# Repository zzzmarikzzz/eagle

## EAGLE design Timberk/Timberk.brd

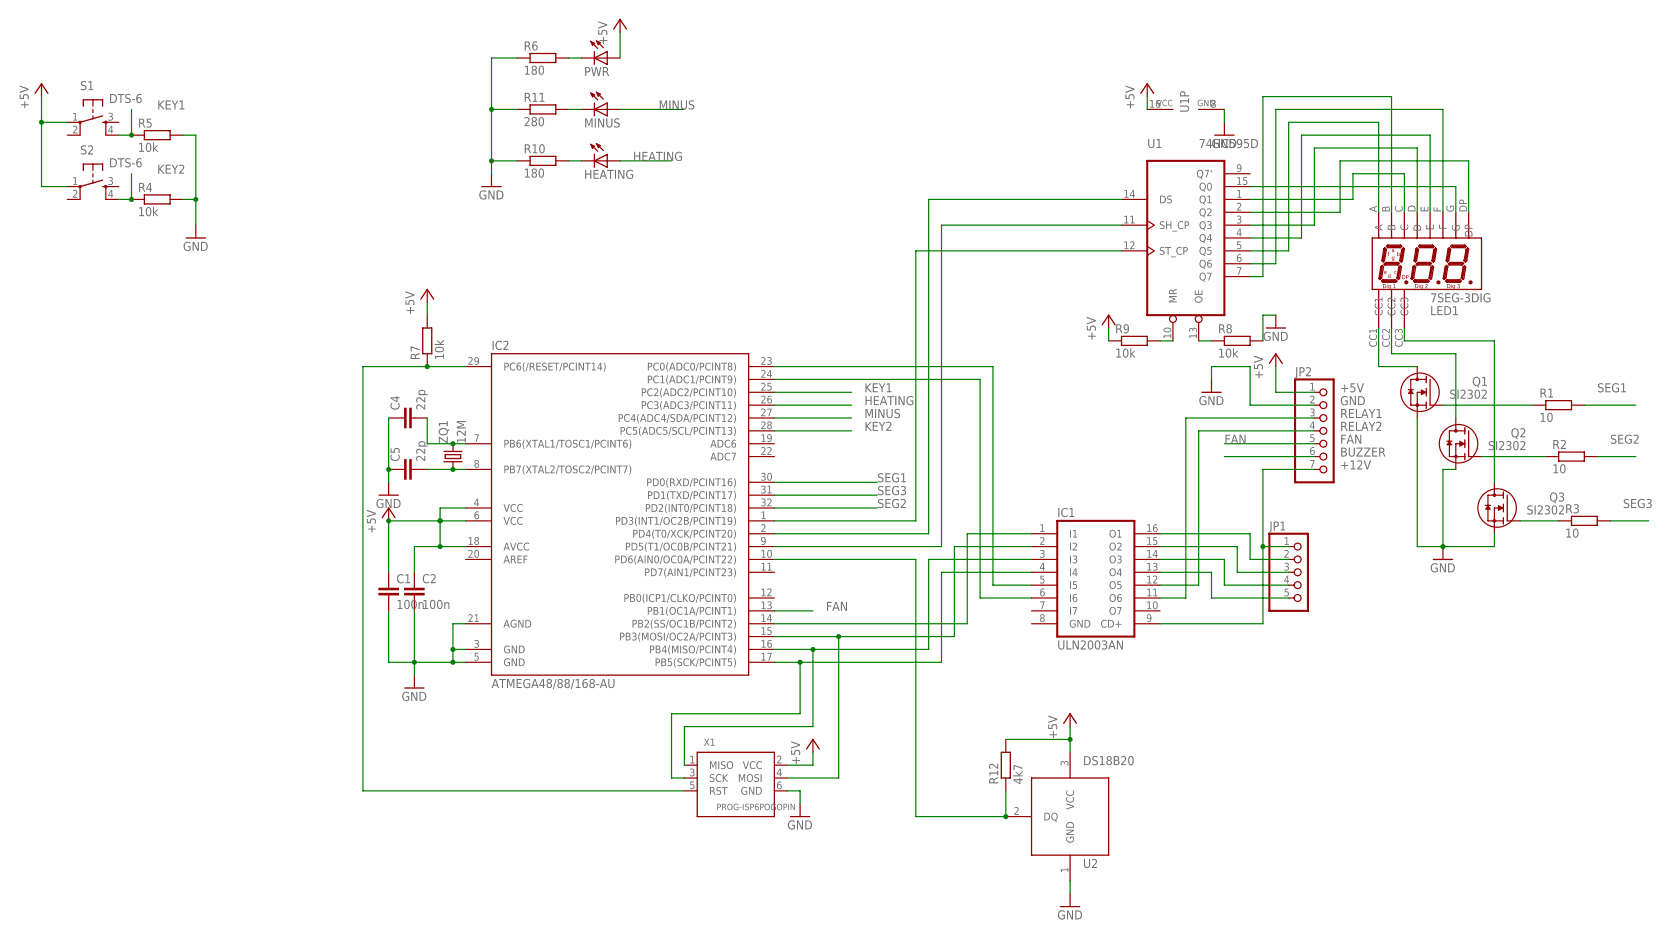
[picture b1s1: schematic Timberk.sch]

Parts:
C1, C2: 100n; C0603
C4, C5: 22p; C0603
HEATING: LED5MM
IC1: ULN2003AN; DIL16
IC2: ATMEGA48/88/168-AU; TQFP32-08
JP1: PINHD-1X5/90; 1X05/90
JP2: PINHD-1X7/90; 1X07/90
LED1: 7SEG-3DIG; 7SEG_3DIG_0.56
MINUS: LED5MM
PWR: LED5MM
Q1, Q2, Q3: SI2302; SOT-23-GSD
R1, R2, R3: 10; R0603
R4, R5, R7, R8, R9: 10k; R0603
R6, R10: 180; R0603
R11: 280; R0603
R12: 4k7; R0603
S1, S2: DTS-6
U1: 74HC595D; SO16
U2: DS18B20; TO92
X1: PROG-ISP6POGOPIN; PROG_POGOPIN
ZQ1: 12M; HC49/S

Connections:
+5V: C1.1, C2.1, IC2.4 (VCC), IC2.6 (VCC), IC2.18 (AVCC), JP2.1, PWR.A, R7.2, R9.1, R12.2, S1.1, S2.1, U1.16 (VCC), U2.3 (VCC), X1.2 (VCC)
+12V: IC1.9 (CD+), JP1.1, JP2.7
BUZZER: JP2.6
FAN: IC2.13 (PB1(OC1A/PCINT1)), JP2.5
GND: C1.2, C2.2, C4.1, C5.1, IC1.8 (GND), IC2.3 (GND), IC2.5 (GND), IC2.21 (AGND), JP2.2, Q1.S, Q2.S, Q3.S, R4.2, R5.2, R6.1, R8.2, R10.1, R11.1, U1.8 (GND), U2.1 (GND), X1.6 (GND)
HEATING: HEATING.A, IC2.26 (PC3(ADC3/PCINT11))
KEY1: IC2.25 (PC2(ADC2/PCINT10)), R5.1, S1.4
KEY2: IC2.28 (PC5(ADC5/SCL/PCINT13)), R4.1, S2.4
MINUS: IC2.27 (PC4(ADC4/SDA/PCINT12)), MINUS.A
unnamed: IC1.13 (O4), JP1.5
unnamed: IC1.14 (O3), JP1.4
unnamed: IC1.15 (O2), JP1.3
unnamed: IC1.16 (O1), JP1.2
unnamed: LED1.C, U1.1 (Q1)
unnamed: LED1.DP, U1.2 (Q2)
unnamed: LED1.G, U1.15 (Q0)
unnamed: LED1.D, U1.3 (Q3)
unnamed: LED1.E, U1.4 (Q4)
unnamed: LED1.A, U1.5 (Q5)
unnamed: LED1.F, U1.6 (Q6)
unnamed: LED1.B, U1.7 (Q7)
unnamed: Q1.G, R1.1
unnamed: Q2.G, R2.1
unnamed: Q3.G, R3.1
unnamed: LED1.CC1, Q1.D
unnamed: LED1.CC2, Q2.D
unnamed: LED1.CC3, Q3.D
unnamed: PWR.K (C), R6.2
unnamed: IC1.1 (I1), IC2.14 (PB2(SS/OC1B/PCINT2))
unnamed: IC1.2 (I2), IC2.15 (PB3(MOSI/OC2A/PCINT3)), X1.4 (MOSI)
unnamed: IC1.6 (I6), IC2.24 (PC1(ADC1/PCINT9))
unnamed: IC1.3 (I3), IC2.16 (PB4(MISO/PCINT4)), X1.1 (MISO)
unnamed: IC1.4 (I4), IC2.17 (PB5(SCK/PCINT5)), X1.3 (SCK)
unnamed: IC2.29 (PC6(/RESET/PCINT14)), R7.1, X1.5 (RST)
unnamed: R9.2, U1.10 (MR)
unnamed: IC2.1 (PD3(INT1/OC2B/PCINT19)), U1.12 (ST_CP)
unnamed: C5.2, IC2.8 (PB7(XTAL2/TOSC2/PCINT7)), ZQ1.1
unnamed: C4.2, IC2.7 (PB6(XTAL1/TOSC1/PCINT6)), ZQ1.2
unnamed: R8.1, U1.13 (OE)
unnamed: IC2.2 (PD4(T0/XCK/PCINT20)), U1.14 (DS)
unnamed: IC2.9 (PD5(T1/OC0B/PCINT21)), U1.11 (SH_CP)
unnamed: IC1.5 (I5), IC2.23 (PC0(ADC0/PCINT8))
unnamed: HEATING.K (C), R10.2
unnamed: MINUS.K (C), R11.2
unnamed: IC2.10 (PD6(AIN0/OC0A/PCINT22)), R12.1, U2.2 (DQ)
RELAY1: IC1.11 (O6), JP2.3
RELAY2: IC1.12 (O5), JP2.4
SEG1: IC2.30 (PD0(RXD/PCINT16)), R1.2
SEG2: IC2.32 (PD2(INT0/PCINT18)), R2.2
SEG3: IC2.31 (PD1(TXD/PCINT17)), R3.2

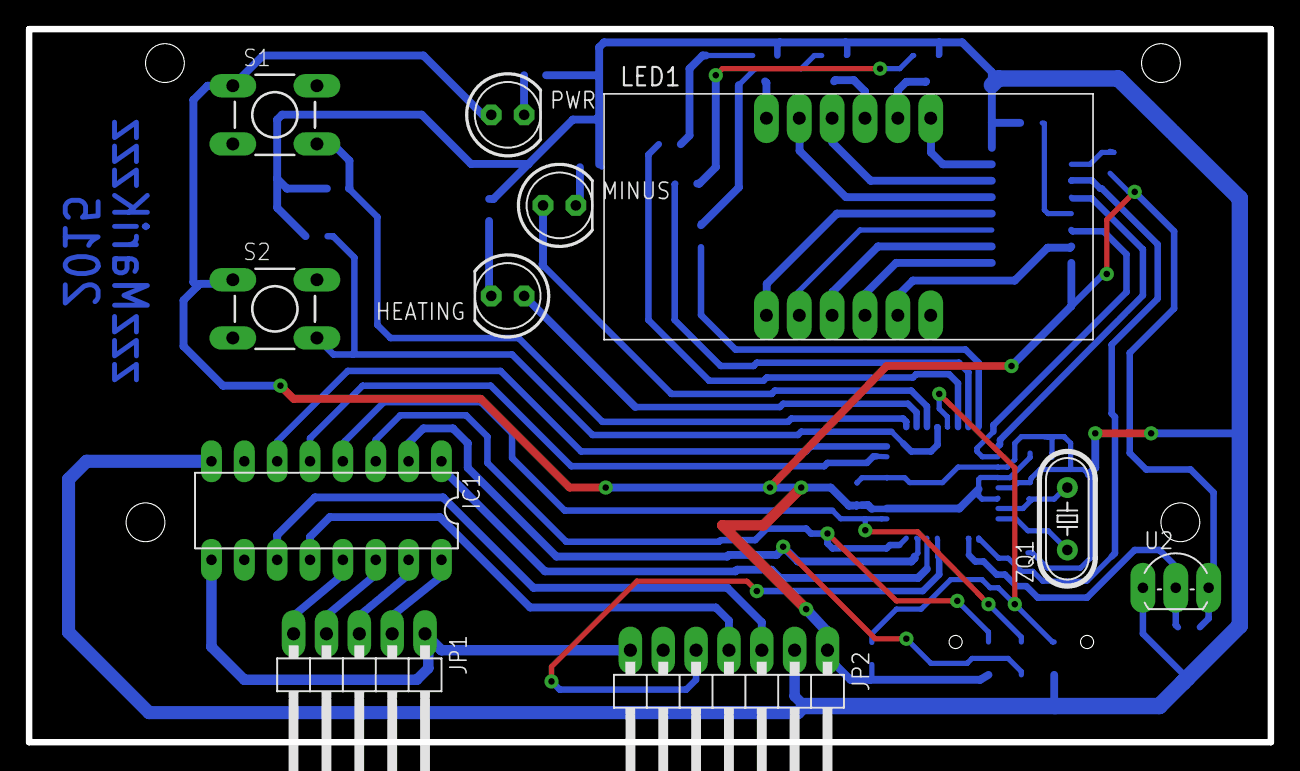
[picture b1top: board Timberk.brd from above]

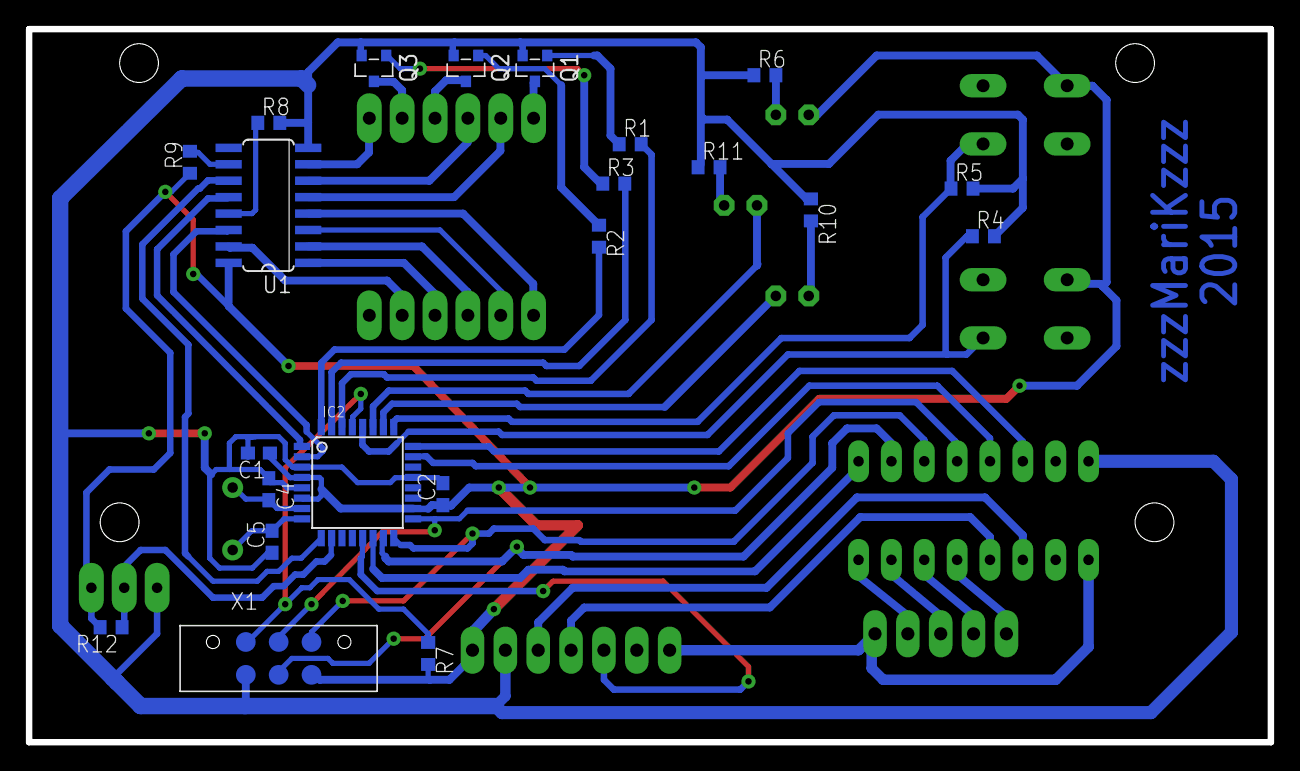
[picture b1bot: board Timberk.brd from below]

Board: 2 copper layers, 96.0 x 55.1 mm, 33 parts (22 on the bottom side), 49 nets.

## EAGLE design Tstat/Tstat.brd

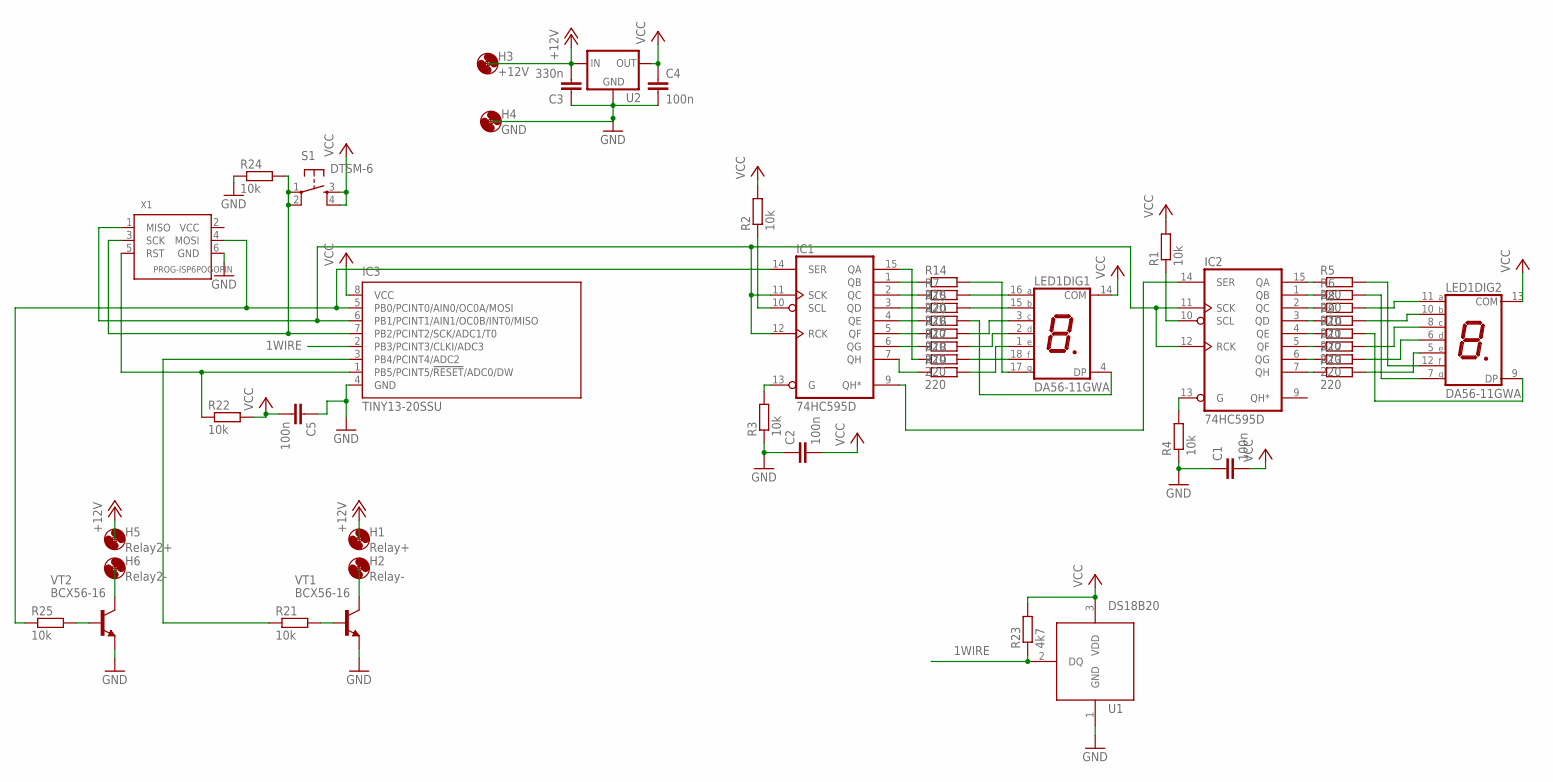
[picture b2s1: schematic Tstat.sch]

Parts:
C1, C2, C4, C5: 100n; C0805
C3: 330n; C0805
H1: Relay+; 3,0
H2: Relay-; 3,0
H3: +12V; 3,0
H4: GND; 3,0
H5: Relay2+; 3,0
H6: Relay2-; 3,0
IC1, IC2: 74HC595D; SO16
IC3: TINY13-20SSU; 8S1
LED1: DA56-11GWA; DA56
R1, R2, R3, R4, R21, R22, R24, R25: 10k; R0603
R5, R6, R7, R8, R9, R10, R11, R12, R13, R14, R15, R16, R17, R18, R19, R20: 220; R0603
R23: 4k7; R0603
S1: DTSM-6
U1: DS18B20; TO92
U2: L78XX/TO263; TO263
VT1, VT2: BCX56-16; SOT89-BCE
X1: PROG-ISP6POGOPIN; PROG_POGOPIN

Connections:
1WIRE: IC3.2 (PB3/PCINT3/CLKI/ADC3), R23.1, U1.2 (DQ)
+12V: C3.2, H1.P$1, H3.P$1, H5.P$1, U2.1 (IN)
GND: C1.1, C2.1, C3.1, C4.2, C5.1, H4.P$1, IC1.8 (GND), IC2.8 (GND), IC3.4 (GND), R3.1, R4.1, R24.1, U1.1 (GND), U2.3 (GND), VT1.E, VT2.E, X1.6 (GND)
unnamed: IC1.15 (QA), R18.1
unnamed: LED1.17 (G), R14.2
unnamed: LED1.16 (A), R7.2
unnamed: LED1.15 (B), R15.2
unnamed: LED1.4 (DP), R20.2
unnamed: LED1.3 (C), R16.2
unnamed: LED1.2 (D), R17.2
unnamed: LED1.1 (E), R19.2
unnamed: LED1.12 (F), R5.2
unnamed: LED1.7 (G), R6.2
unnamed: LED1.11 (A), R8.2
unnamed: LED1.10 (B), R9.2
unnamed: LED1.9 (DP), R10.2
unnamed: LED1.8 (C), R11.2
unnamed: LED1.6 (D), R12.2
unnamed: LED1.5 (E), R13.2
unnamed: IC1.9 (QH*), IC2.14 (SER)
unnamed: IC2.10 (SCL), R1.1
unnamed: IC2.13 (G), R4.2
unnamed: IC1.13 (G), R3.2
unnamed: IC1.10 (SCL), R2.1
unnamed: IC2.15 (QA), R5.1
unnamed: IC1.11 (SCK), IC1.12 (RCK), IC2.11 (SCK), IC2.12 (RCK), IC3.6 (PB1/PCINT1/AIN1/OC0B/INT0/MISO), X1.1 (MISO)
unnamed: IC2.1 (QB), R6.1
unnamed: IC2.2 (QC), R8.1
unnamed: IC2.3 (QD), R9.1
unnamed: IC2.4 (QE), R10.1
unnamed: IC2.5 (QF), R11.1
unnamed: IC2.6 (QG), R12.1
unnamed: IC2.7 (QH), R13.1
unnamed: IC1.1 (QB), R14.1
unnamed: IC1.2 (QC), R7.1
unnamed: IC1.3 (QD), R15.1
unnamed: IC1.5 (QF), R16.1
unnamed: IC1.6 (QG), R17.1
unnamed: LED1.18 (F), R18.2
unnamed: IC1.7 (QH), R19.1
unnamed: IC1.4 (QE), R20.1
unnamed: H2.P$1, VT1.C, VT1.C@1 (C)
unnamed: R21.2, VT1.B
unnamed: IC1.14 (SER), IC3.5 (PB0/PCINT0/AIN0/OC0A/MOSI), R25.1, X1.4 (MOSI)
unnamed: H6.P$1, VT2.C, VT2.C@1 (C)
unnamed: IC3.7 (PB2/PCINT2/SCK/ADC1/T0), R24.2, S1.1, S1.2, X1.3 (SCK)
unnamed: IC3.1 (PB5/PCINT5/!RESET!/ADC0/DW), R22.1, X1.5 (RST)
unnamed: R25.2, VT2.B
unnamed: IC3.3 (PB4/PCINT4/ADC2), R21.1
VCC: C1.2, C2.2, C4.1, C5.2, IC1.16 (VCC), IC2.16 (VCC), IC3.8 (VCC), LED1.13 (COM), LED1.14 (COM), R1.2, R2.2, R22.2, R23.2, S1.3, S1.4, U1.3 (VDD), U2.2 (OUT)

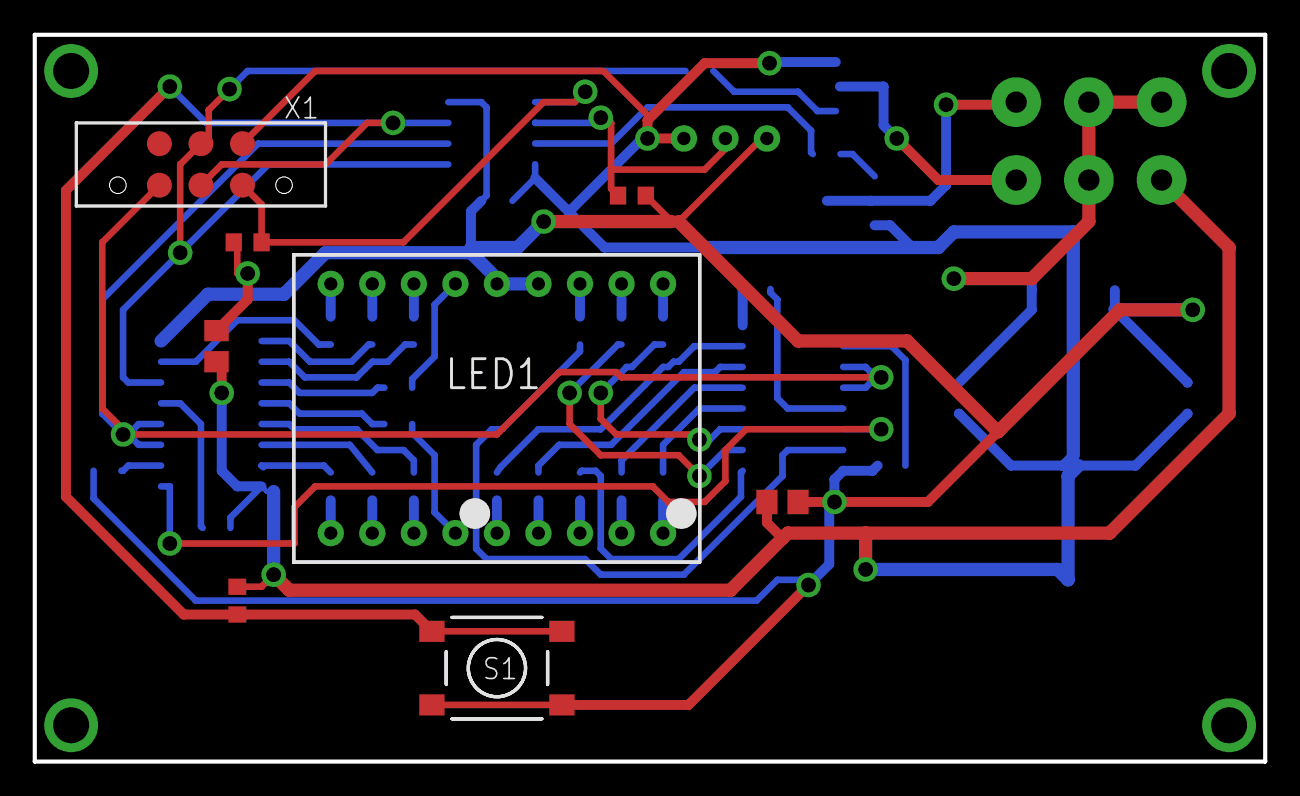
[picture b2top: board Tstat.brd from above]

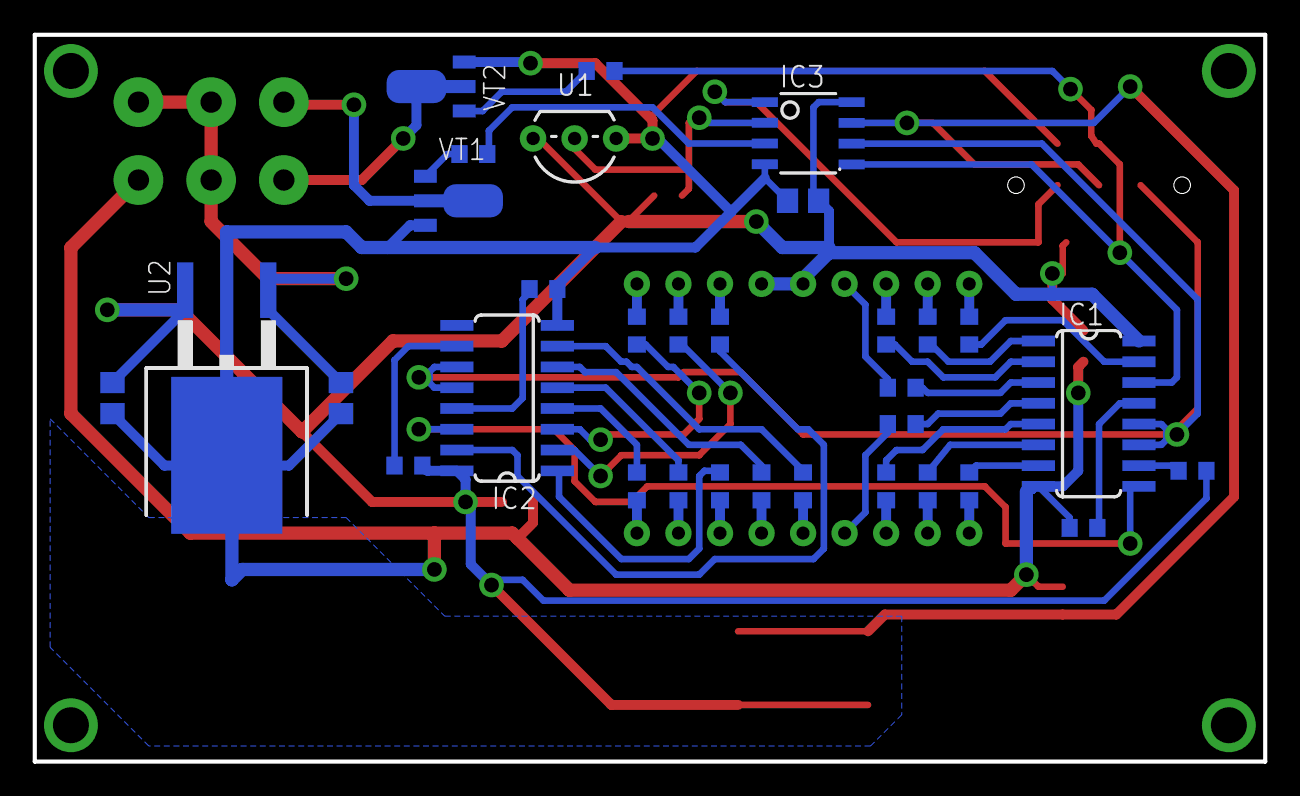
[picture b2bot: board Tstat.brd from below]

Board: 2 copper layers, 75.2 x 44.4 mm, 46 parts (32 on the bottom side), 50 nets.

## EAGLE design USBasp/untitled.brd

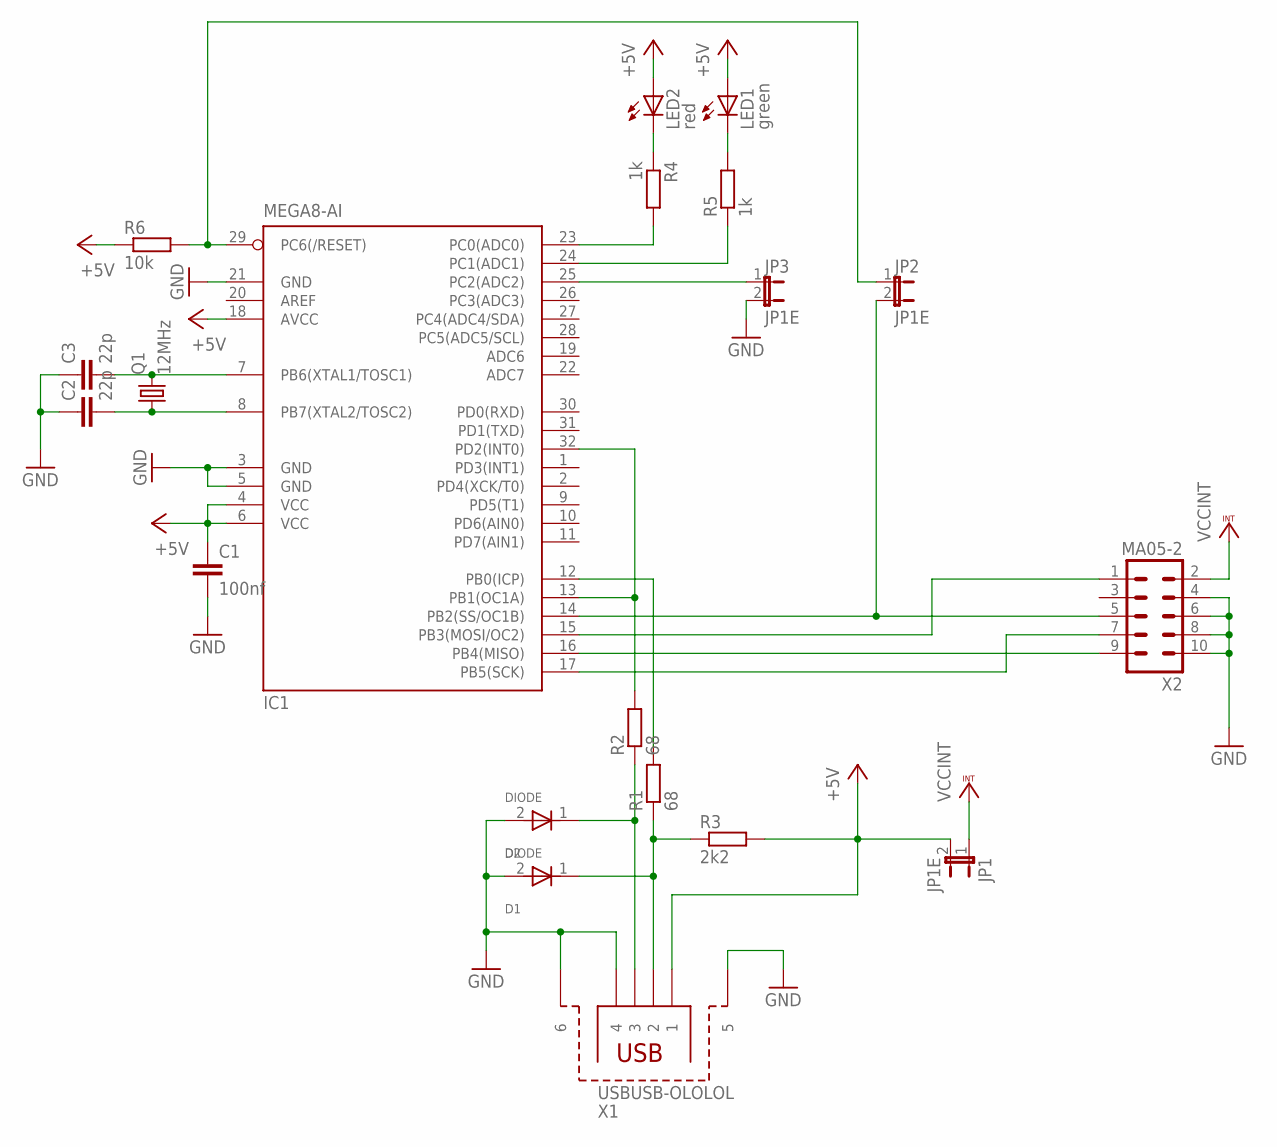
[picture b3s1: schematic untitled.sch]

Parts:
C1: 100nf; C0805
C2, C3: 22p; C0805
D1, D2: DIODE; SOD80
IC1: MEGA8-AI; TQFP32-08
JP1, JP2, JP3: JP1E; JP0603
LED1: green; CHIPLED_0805
LED2: red; CHIPLED_0805
Q1: 12MHz; HC49/S
R1, R2: 68; R0603
R3: 2k2; R0603
R4, R5: 1k; R0603
R6: 10k; R0603
X1: USBUSB-OLOLOL; USB
X2: MA05-2

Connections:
+5V: C1.1, IC1.4 (VCC), IC1.6 (VCC), IC1.18 (AVCC), JP1.2, LED1.A, LED2.A, R3.2, R6.1, X1.1
GND: C1.2, C2.1, C3.1, D1.2 (ANOD), D2.2 (ANOD), IC1.3 (GND), IC1.5 (GND), IC1.21 (GND), JP3.2, X1.4, X1.5, X1.6, X2.4, X2.6, X2.8, X2.10
unnamed: IC1.23 (PC0(ADC0)), R4.2
unnamed: LED2.C, R4.1
unnamed: LED1.C, R5.2
unnamed: IC1.24 (PC1(ADC1)), R5.1
unnamed: IC1.25 (PC2(ADC2)), JP3.1
unnamed: IC1.29 (PC6(/RESET)), JP2.1, R6.2
unnamed: C2.2, IC1.8 (PB7(XTAL2/TOSC2)), Q1.1
unnamed: IC1.14 (PB2(SS/OC1B)), JP2.2, X2.5
unnamed: IC1.15 (PB3(MOSI/OC2)), X2.1
unnamed: IC1.17 (PB5(SCK)), X2.7
unnamed: IC1.16 (PB4(MISO)), X2.9
unnamed: C3.2, IC1.7 (PB6(XTAL1/TOSC1)), Q1.2
unnamed: D1.1 (KATOD), R1.1, R3.1, X1.2
unnamed: D2.1 (KATOD), R2.1, X1.3
unnamed: IC1.13 (PB1(OC1A)), IC1.32 (PD2(INT0)), R2.2
unnamed: IC1.12 (PB0(ICP)), R1.2
VCCINT: JP1.1, X2.2

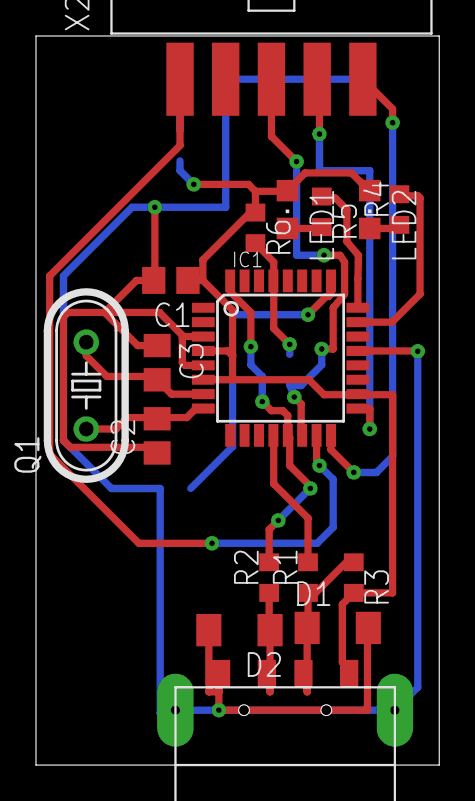
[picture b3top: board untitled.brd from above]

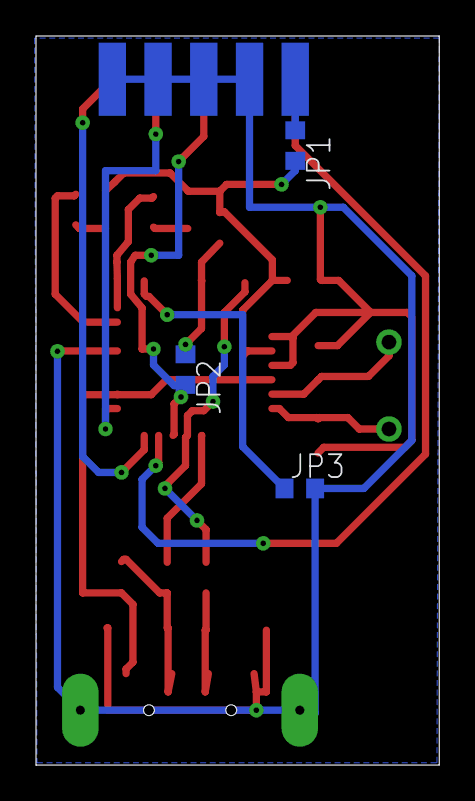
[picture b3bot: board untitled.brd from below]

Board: 2 copper layers, 22.4 x 40.5 mm, 20 parts (3 on the bottom side), 19 nets.

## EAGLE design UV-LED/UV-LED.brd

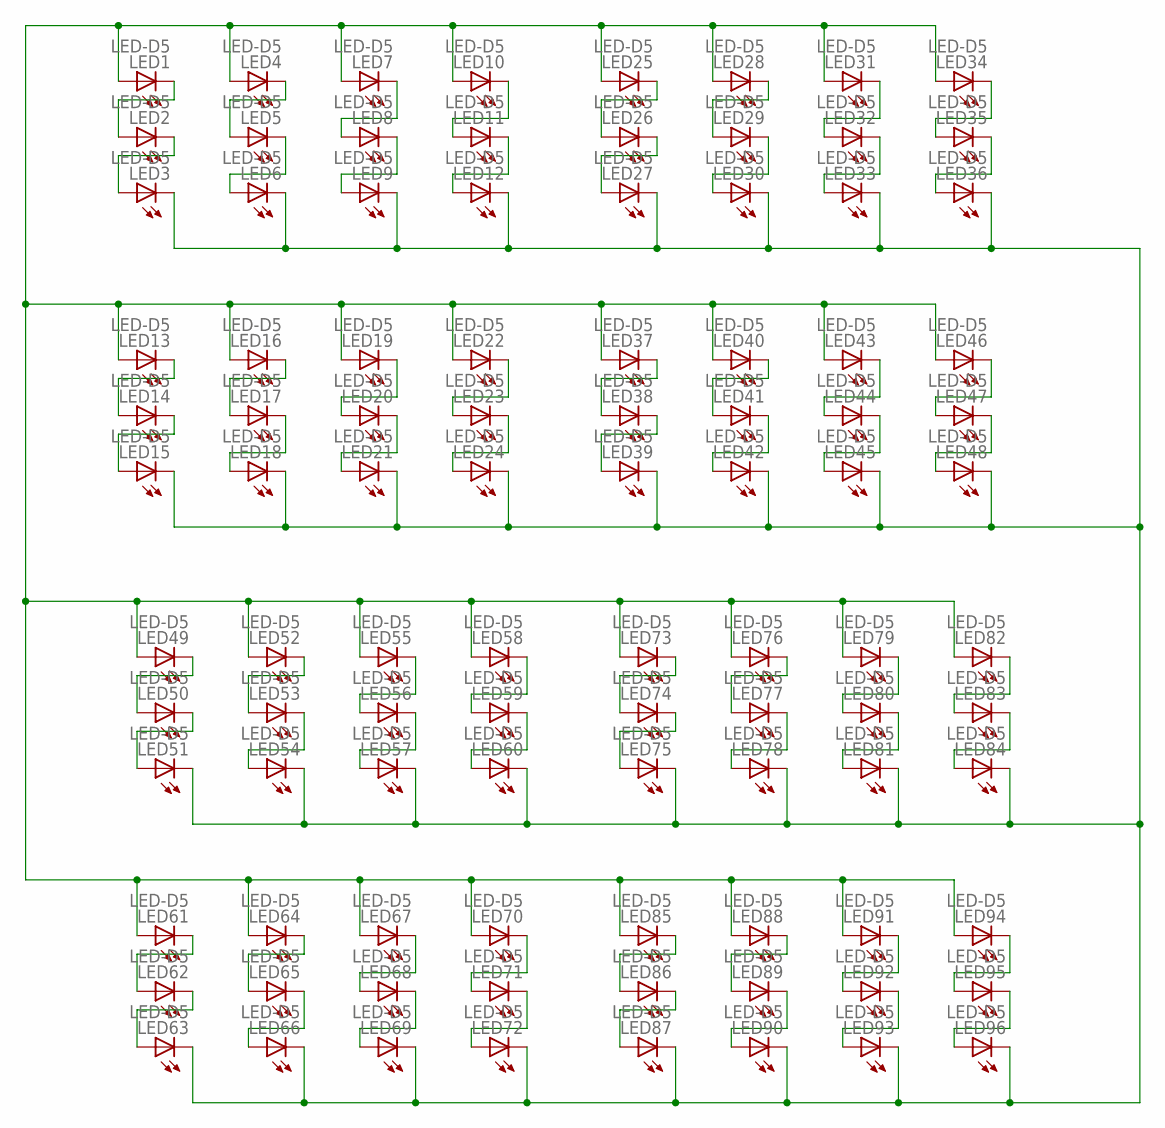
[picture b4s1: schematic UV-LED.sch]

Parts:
LED1, LED2, LED3, LED4, LED5, LED6, LED7, LED8, LED9, LED10, LED11, LED12, LED13, LED14, LED15, LED16, LED17, LED18, LED19, LED20, LED21, LED22, LED23, LED24, LED25, LED26, LED27, LED28, LED29, LED30, LED31, LED32, LED33, LED34, LED35, LED36, LED37, LED38, LED39, LED40, LED41, LED42, LED43, LED44, LED45, LED46, LED47, LED48, LED49, LED50, LED51, LED52, LED53, LED54, LED55, LED56, LED57, LED58, LED59, LED60, LED61, LED62, LED63, LED64, LED65, LED66, LED67, LED68, LED69, LED70, LED71, LED72, LED73, LED74, LED75, LED76, LED77, LED78, LED79, LED80, LED81, LED82, LED83, LED84, LED85, LED86, LED87, LED88, LED89, LED90, LED91, LED92, LED93, LED94, LED95, LED96: LED-D5

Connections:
unnamed: LED1.A, LED4.A, LED7.A, LED10.A, LED13.A, LED16.A, LED19.A, LED22.A, LED25.A, LED28.A, LED31.A, LED34.A, LED37.A, LED40.A, LED43.A, LED46.A, LED49.A, LED52.A, LED55.A, LED58.A, LED61.A, LED64.A, LED67.A, LED70.A, LED73.A, LED76.A, LED79.A, LED82.A, LED85.A, LED88.A, LED91.A, LED94.A
unnamed: LED1.C, LED2.A
unnamed: LED2.C, LED3.A
unnamed: LED4.C, LED5.A
unnamed: LED5.C, LED6.A
unnamed: LED7.C, LED8.A
unnamed: LED8.C, LED9.A
unnamed: LED10.C, LED11.A
unnamed: LED11.C, LED12.A
unnamed: LED13.C, LED14.A
unnamed: LED14.C, LED15.A
unnamed: LED16.C, LED17.A
unnamed: LED17.C, LED18.A
unnamed: LED19.C, LED20.A
unnamed: LED20.C, LED21.A
unnamed: LED22.C, LED23.A
unnamed: LED23.C, LED24.A
unnamed: LED3.C, LED6.C, LED9.C, LED12.C, LED15.C, LED18.C, LED21.C, LED24.C, LED27.C, LED30.C, LED33.C, LED36.C, LED39.C, LED42.C, LED45.C, LED48.C, LED51.C, LED54.C, LED57.C, LED60.C, LED63.C, LED66.C, LED69.C, LED72.C, LED75.C, LED78.C, LED81.C, LED84.C, LED87.C, LED90.C, LED93.C, LED96.C
unnamed: LED25.C, LED26.A
unnamed: LED26.C, LED27.A
unnamed: LED28.C, LED29.A
unnamed: LED29.C, LED30.A
unnamed: LED31.C, LED32.A
unnamed: LED32.C, LED33.A
unnamed: LED34.C, LED35.A
unnamed: LED35.C, LED36.A
unnamed: LED37.C, LED38.A
unnamed: LED38.C, LED39.A
unnamed: LED40.C, LED41.A
unnamed: LED41.C, LED42.A
unnamed: LED43.C, LED44.A
unnamed: LED44.C, LED45.A
unnamed: LED46.C, LED47.A
unnamed: LED47.C, LED48.A
unnamed: LED49.C, LED50.A
unnamed: LED50.C, LED51.A
unnamed: LED52.C, LED53.A
unnamed: LED53.C, LED54.A
unnamed: LED55.C, LED56.A
unnamed: LED56.C, LED57.A
unnamed: LED58.C, LED59.A
unnamed: LED59.C, LED60.A
unnamed: LED61.C, LED62.A
unnamed: LED62.C, LED63.A
unnamed: LED64.C, LED65.A
unnamed: LED65.C, LED66.A
unnamed: LED67.C, LED68.A
unnamed: LED68.C, LED69.A
unnamed: LED70.C, LED71.A
unnamed: LED71.C, LED72.A
unnamed: LED73.C, LED74.A
unnamed: LED74.C, LED75.A
unnamed: LED76.C, LED77.A
unnamed: LED77.C, LED78.A
unnamed: LED79.C, LED80.A
unnamed: LED80.C, LED81.A
unnamed: LED82.C, LED83.A
unnamed: LED83.C, LED84.A
unnamed: LED85.C, LED86.A
unnamed: LED86.C, LED87.A
unnamed: LED88.C, LED89.A
unnamed: LED89.C, LED90.A
unnamed: LED91.C, LED92.A
unnamed: LED92.C, LED93.A
unnamed: LED94.C, LED95.A
unnamed: LED95.C, LED96.A

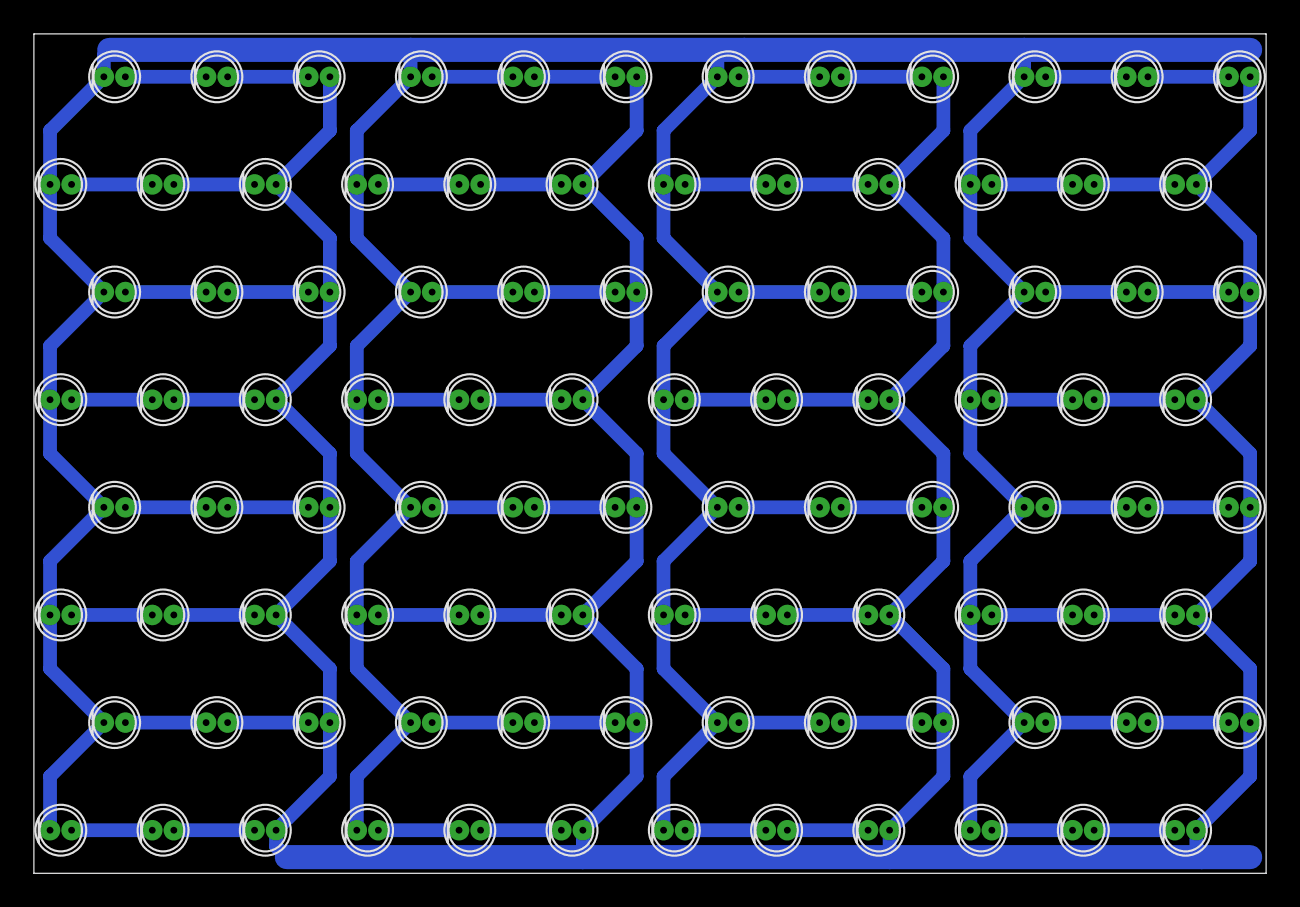
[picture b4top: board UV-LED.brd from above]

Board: 2 copper layers, 72.7 x 49.5 mm, 96 parts (0 on the bottom side), 66 nets.

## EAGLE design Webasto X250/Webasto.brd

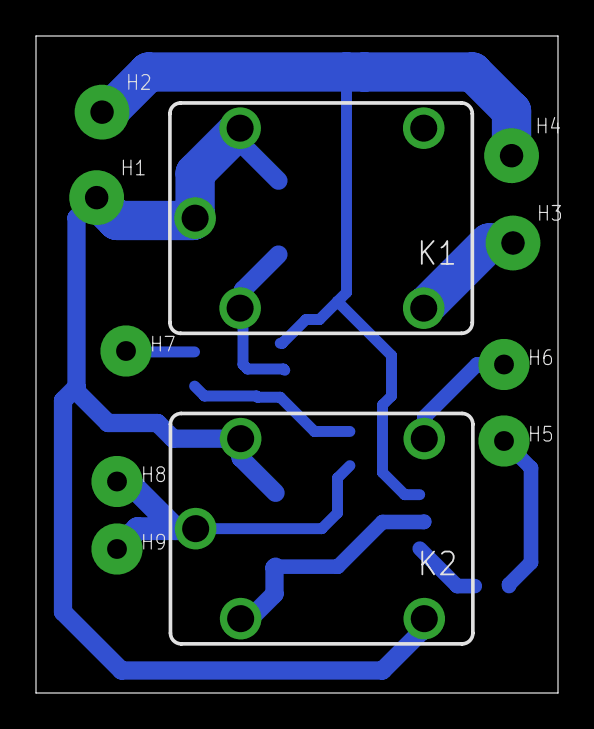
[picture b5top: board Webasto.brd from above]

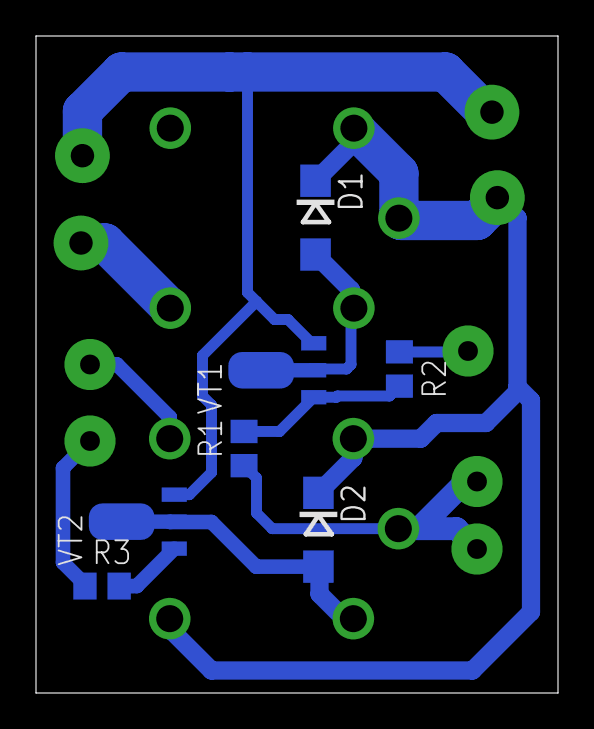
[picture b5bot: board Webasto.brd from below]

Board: 2 copper layers, 29.0 x 36.5 mm, 18 parts (7 on the bottom side), 11 nets.

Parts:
D1, D2: DIODESMD; DO214AC
H1: +12V; 3,0
H2: GND; 3,0
H3: Pump 12V; 3,0
H4: Pump GND; 3,0
H5: Timer; 2,8
H6: Generator; 2,8
H7: Web. FAN; 2,8
H8: Web. CANTROL; 2,8
H9: Cab. FAN; 2,8
K1, K2: CQ1-12V; CQ1
R1, R2, R3: 10k; R0805
VT1, VT2: BCX56-16; SOT89-BCE

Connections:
+12V: D1.C, D2.C, H1.P$1, K1.1, K1.C, K2.1, K2.NO
GND: H2.P$1, H4.P$1, VT1.E, VT2.E
unnamed: H7.P$1, R2.1
unnamed: D1.A, K1.2, VT1.C, VT1.C@1
unnamed: R1.2, R2.2, VT1.B
unnamed: D2.A, K2.2, VT2.C, VT2.C@1
unnamed: R3.2, VT2.B
unnamed: H8.P$1, H9.P$1, K2.C, R1.1
unnamed: H5.P$1, R3.1
unnamed: H3.P$1, K1.NO
unnamed: H6.P$1, K2.NC
